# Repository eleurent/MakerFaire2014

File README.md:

Mission on Mars Robot Challenge - Maker Faire 2014
=================

*Alexandre Lefort, Martin de Gourcuff, Edouard Leurent* - Psittacidae team

# Features

## InputProcessing
- Implementation of an Extended Kalman Filter to estimate position and orientation by updating odometry with computer vision.
- Implementation of an Unscented Kalman Filter for the same purpose, more efficient than the EKF for state update after an important dift (with added noise in the encoders, for instance), but more computationally expensive.
- The camera observation with EKF/UKF uses all targets detected by the camera, and not just the destination as in the original simulation.
- The camera delay (0.3s) is now taken into account in the EKF/UKF.
- Distance command is now handled as a relative command to handle overshoots and turns.
- Rotation during the validation time at a target pour to face the next target.

## Controller
- More aggressive gains tuning
- Priorization of the angle command by dynamic saturation of the distance command at the maximum allowing the bearing command differential.
- Add integral gains in distance and bearing to avoid being stuck near a target because of the motor dead bands.
  The integral term is bounded for bearing to avoid wind-up phenomenon.
- Add a derivative term to the bearing controller, when the robot is stopped, to avoir overshoots.
- Two different sets of gains are used in the bearing controller when the robot is stopped or in motion.

## Strategy
- Travelling salesman solver using a genetic algorithm to find the shortest route.

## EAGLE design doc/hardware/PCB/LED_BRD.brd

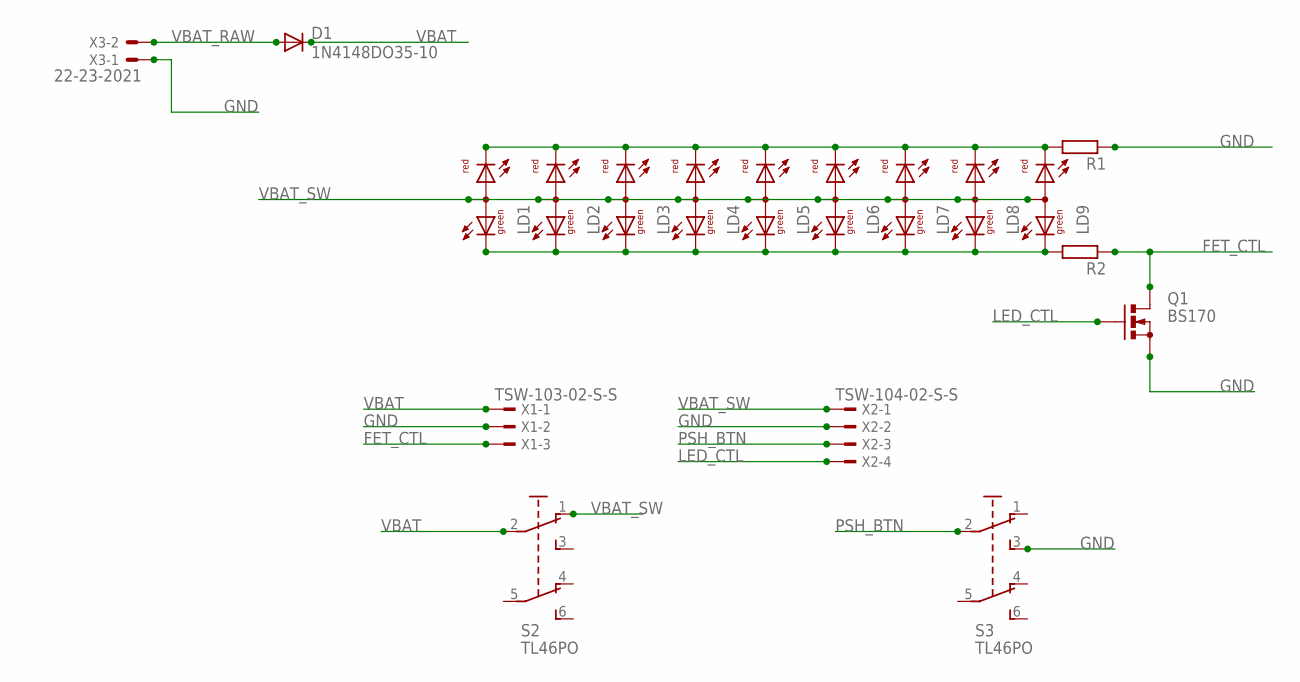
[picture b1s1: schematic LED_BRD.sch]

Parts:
D1: 1N4148DO35-10; DO35-10
LD1, LD2, LD3, LD4, LD5, LD6, LD7, LD8, LD9: DUOLED-RG-A; DUOLED-A-5MM
Q1: BS170; SOT54E
R1, R2: R0204/7; 0204/7
S2, S3: TL46PO; TL4XPO
X1: TSW-103-02-S-S
X2: TSW-104-02-S-S
X3: 22-23-2021

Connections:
FET_CTL: Q1.D, R2.1, X1.3
GND: Q1.S, R1.1, S3.3 (S), X1.2, X2.2, X3.1
LED_CTL: Q1.G, X2.4
unnamed: LD1.CX (CG), LD2.CX (CG), LD3.CX (CG), LD4.CX (CG), LD5.CX (CG), LD6.CX (CG), LD7.CX (CG), LD8.CX (CG), LD9.CX (CG), R2.2
unnamed: LD1.CR, LD2.CR, LD3.CR, LD4.CR, LD5.CR, LD6.CR, LD7.CR, LD8.CR, LD9.CR, R1.2
PSH_BTN: S3.2, X2.3
VBAT: D1.C, S2.2, X1.1
VBAT_RAW: D1.A, X3.2
VBAT_SW: LD1.A, LD2.A, LD3.A, LD4.A, LD5.A, LD6.A, LD7.A, LD8.A, LD9.A, S2.1 (O), X2.1

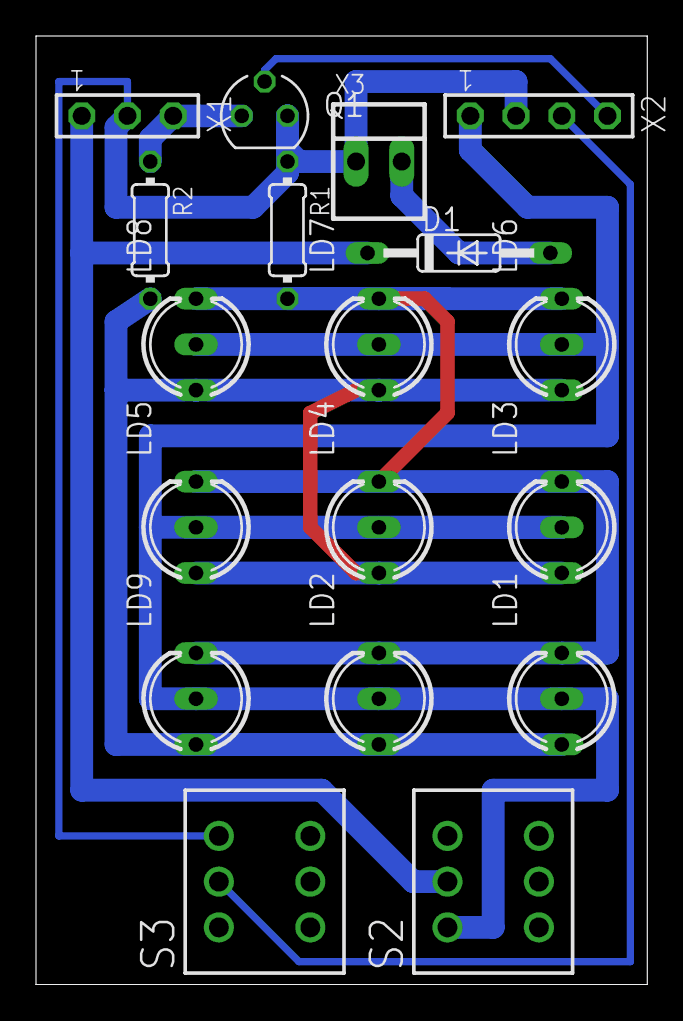
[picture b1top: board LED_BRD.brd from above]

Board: 2 copper layers, 34.0 x 52.7 mm, 18 parts (0 on the bottom side), 9 nets.

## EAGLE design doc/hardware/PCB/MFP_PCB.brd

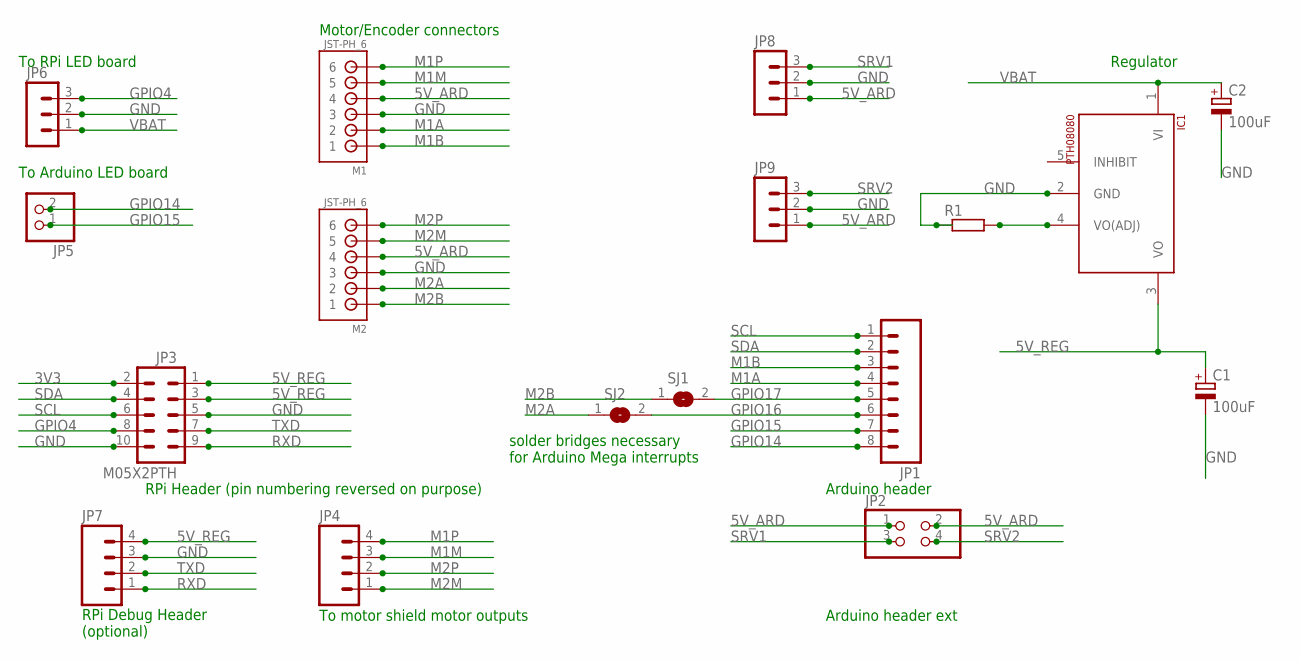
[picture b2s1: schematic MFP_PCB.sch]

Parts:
C1, C2: 100uF; 150CLZ-0810
IC1: PTH08080
JP1: M08LONGPADS; 1X08_LONGPADS
JP2: PINHD-2X2; 2X02
JP3: M05X2PTH; AVR_ICSP
JP4, JP7: M04PTH; 1X04
JP5: PINHD-1X2; 1X02
JP6, JP8, JP9: MA03-1
M1, M2: JST-PH_6; JST_B6B-PH_HEADER
R1: R0204/7; 0204/7
SJ1, SJ2: SJ

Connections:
3V3: JP3.2
5V_ARD: JP2.1, JP2.2, JP8.1, JP9.1, M1.P4 (4), M2.P4 (4)
5V_REG: C1.+, IC1.3 (VO), JP3.1, JP3.3, JP7.4
GND: C1.-, C2.-, IC1.2 (GND), JP3.5, JP3.10, JP6.2, JP7.3, JP8.2, JP9.2, M1.P3 (3), M2.P3 (3), R1.1
GPIO4: JP3.8, JP6.3
GPIO14: JP1.8, JP5.2
GPIO15: JP1.7, JP5.1
GPIO16: JP1.6, SJ2.2
GPIO17: JP1.5, SJ1.2
M1A: JP1.4, M1.P2 (2)
M1B: JP1.3, M1.P1 (1)
M1M: JP4.3, M1.P5 (5)
M1P: JP4.4, M1.P6 (6)
M2A: M2.P2 (2), SJ2.1
M2B: M2.P1 (1), SJ1.1
M2M: JP4.1, M2.P5 (5)
M2P: JP4.2, M2.P6 (6)
unnamed: IC1.4 (VO(ADJ)), R1.2
RXD: JP3.9, JP7.1
SCL: JP1.1, JP3.6
SDA: JP1.2, JP3.4
SRV1: JP2.3, JP8.3
SRV2: JP2.4, JP9.3
TXD: JP3.7, JP7.2
VBAT: C2.+, IC1.1 (VI), JP6.1

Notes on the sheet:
To motor shield motor outputs
Arduino header
RPi Header (pin numbering reversed on purpose)
To RPi LED board
To Arduino LED board
Motor/Encoder connectors
solder bridges necessary for Arduino Mega interrupts
RPi Debug Header (optional)
Regulator
Arduino header ext

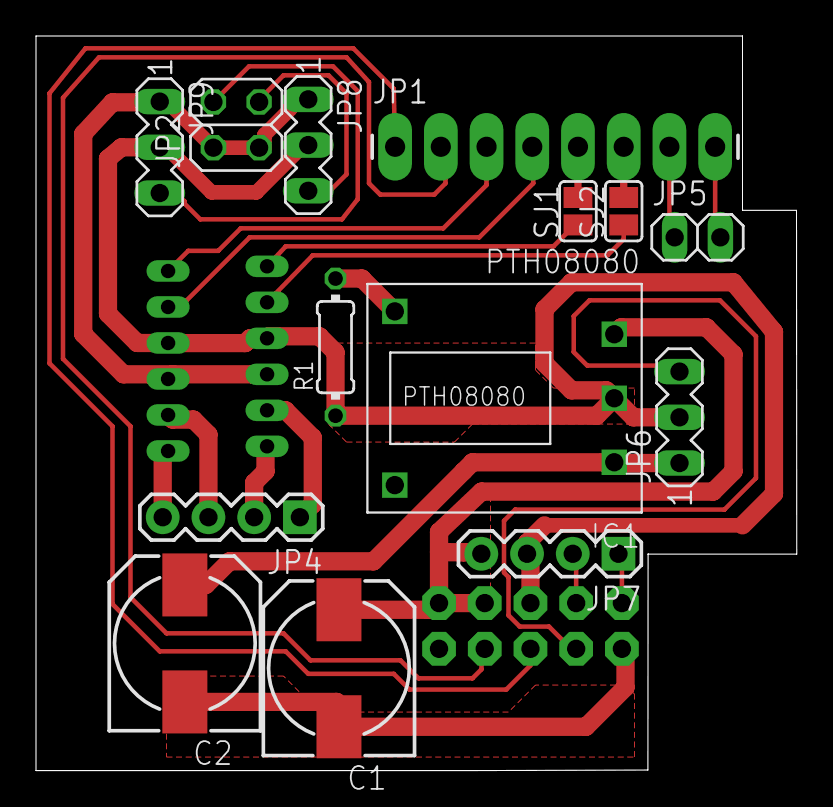
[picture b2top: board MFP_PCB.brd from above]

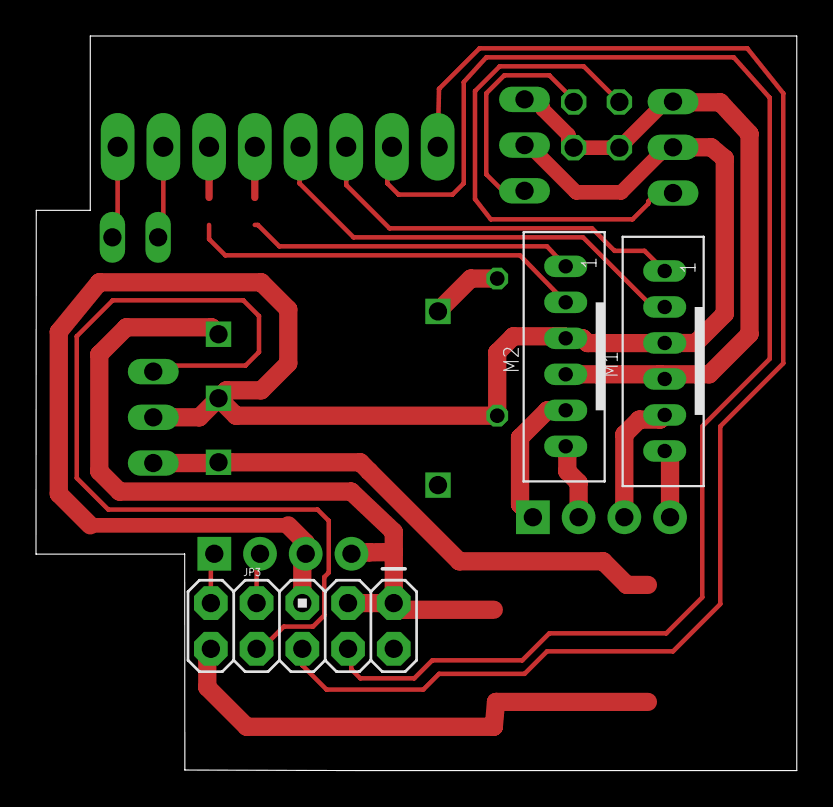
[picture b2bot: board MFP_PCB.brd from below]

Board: 2 copper layers, 42.3 x 40.8 mm, 17 parts (3 on the bottom side), 24 nets.

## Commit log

2014-04-28 Add to version control files related to Simulation
2014-04-29 Insert last version of Prise en main (PDF) and correction on SimulationModel to be commited on GitHub
2014-04-29 Remove some .SimulinkProject files from GitHub
2014-04-29 Remove some files of .SimulinkProject folder from GitHub
2014-04-30 Add Copyright
2014-05-12 adding PCB and robot design files
2014-05-14 Adding BOM
2014-05-21 Todo list
2014-05-29 InputProcessing : Extended Kalman Filter for odometry + Turn while waiting
2014-05-30 Took camera delay into account in EKF update + updated todo list
2014-05-30 Fixed bearing observation not being wrapped to pi
2014-05-31 Fixed EKF and added UKF (now used, slightly more accurate)
2014-05-31 Clamped integral command for bearing in waiting state only
2014-05-31 Fixed integral bearing in stop state
2014-05-31 Adding integral gain for distance
2014-05-31 Genetic algorithm for TSP
2014-05-31 Optimized Output for ga_tsp
2014-05-31 Fix bug toupie + fix bug ga tsp y coordinates
2014-05-31 Oooops, forgot to save
2014-05-31 Quelques changements sur le contrôleur et temps d'attente=2.3s
2014-05-31 Updated todo list and moved ga tsp solver
2014-06-01 Moved ga_tsp, and added utility script. Bearing derivative + Integral reset
2014-06-01 Updated README with our improvements
2014-06-01 updtae du README, ajout de commentaires et supression du scope dans le contrôleur
2014-06-04 Always saturate distance command
2014-06-04 Inversed robot dynamic in controller block
2014-06-05 Reculer pendant l'attente, pour sortir des zones avec une vitesse maximale
2014-06-05 Added inverse motors models (linearized around zero)
2014-06-11 Updated to Mathworks last version, including odometry noise
2014-06-14 Better process noise + estimated trajectory in tracking app
2014-06-20 C-Day
2014-06-20 Changed no-slip odometry gain

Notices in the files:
parts and their libraries:
SparkFun-Connectors: Licensing: Creative Commons ShareAlike 4.0 International - https://creativecommons.org/licenses/by-sa/4.0
